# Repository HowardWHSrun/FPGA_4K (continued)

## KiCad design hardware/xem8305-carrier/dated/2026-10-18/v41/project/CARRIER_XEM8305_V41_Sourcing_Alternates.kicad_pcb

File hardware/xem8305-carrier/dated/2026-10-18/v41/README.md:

# XEM8305 carrier V41 — review package

18 October 2026. **Latest saved carrier revision for Gerald's review; fabrication approval is pending.** This is the carrier that connects the XEM8305 to the existing LDO board. It is separate from the standalone FPGA V41, which shares the same version number.

- [Schematic PDF](output/pdf/Carrier_V41_Schematic.pdf)
- [All six copper layers and both silkscreens](output/layers/README.md)
- [Complete public KiCad ZIP](Carrier_V41_Public_KiCad_Review.zip)
- [Native KiCad project](project/CARRIER_XEM8305_V41_Sourcing_Alternates.kicad_pro)
- [Weekend changes, checks and review questions](Review_Context.md)
- [Factory and assembly requirements](Factory_Review_Requirements.md)
- [V41 BOM: 39 groups / 82 fitted references](output/assembly/V41_JLC_BOM_Full_82_Parts_39_MPNs.csv)
- [Placement file](output/assembly/V41_JLC_CPL_Full_82_Parts_Centroids.csv) and [separate shunt accessory](output/assembly/V41_JP1_Shunt_Accessory_Separate.csv)
- [Gerbers, paste and separate PTH/NPTH drills](output/V41_JLC_Gerber_Paste_Drill_Clean.zip)
- [Verification files](verification/)

Extract the complete ZIP before opening the project in KiCad 10.0.6. Keep its project-local libraries and tables together. This public adaptation omits all 3D model references and embedded supplier STEP bodies; the original local V41 is preserved. The schematic, electrical layout, placements, copper, saved fills, stack and rules are checked against the frozen V41 source. The PCB file's complete hash therefore differs from the private source. Missing 3D bodies cannot establish mechanical clearance.

V41 updates ten references in six sourcing groups after capacitor, LED resistor and EEPROM checks. **All V40 routing remains unchanged:** 738 track sections, 312 vias, 651 pads and 21 zones. The earlier silkscreen cleanup, regulator return correction, USB TVS change and JP1 hole/mechanical adaptation are retained.

Saved-board checks report zero physical/silkscreen findings, zero opens and zero schematic/PCB parity findings under the retained settings. Fifty inherited library warnings and 210 inherited unused-connector ERC findings remain documented. Static checks do not establish powered operation, timing, SI/PI, thermal performance or factory acceptance.

Five assembled boards are being quoted. Four exact-part procurement groups, source allocation and the factory stack/via/panel/manual-assembly review remain open. No procurement, order or payment has been made. The included manufacturing files are review candidates, not an approved production release.

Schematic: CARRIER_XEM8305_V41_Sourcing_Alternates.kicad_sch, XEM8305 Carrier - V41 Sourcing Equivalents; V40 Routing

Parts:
C5: 220 uF / 25 V; EEE_FK1E221P; MPN EEE-FK1E221P
C6, C38, C48: 0.1 uF / 50 V; C_0402; MPN CL05B104KB54PNC
C34, C53: 0.1 uF / 10 V; C_0402; MPN C0402C104K8PACTU
C47: 22 uF / 35 V; C_1206; MPN C3216X5R1V226MTJ00E
C49, C50: 22 uF / 10 V; C_1206; MPN LMK316AB7226KL-TR
C54: 10 pF / 50 V; C_0402; MPN CL05C100JB5NNNC
C55: 3.3 nF / 50 V; C_0402; MPN C0402C332K5RACTU
C56: 1 uF / 25 V X7R; C_0603_1608Metric; MPN MSAST168SB7105KTNA01
C500, C501, C505, C511, C513: 4.7uF; C_0402_1005Metric; MPN JMK105BBJ475MV-F
C502, C503, C504, C506, C507, C508, C509, C512, C514, C515, C516, C517, C518, C519, C520, C522, C525, C526, C527, C528: 100nF; C_0402_1005Metric; MPN C0402C104K8PACTU
C510, C521: 10nF; C_0402_1005Metric; MPN CL05B103KB5NNNC
C523, C524: 18pF; C_0402_1005Metric; MPN C0402C180J5GACTU
D4: SMBJ15CA-13-F; D_SMB; MPN SMBJ15CA-13-F
D500: D5V0FS4U10LP-7; Diodes_UDFN-10_1x2.5mm_P0.5mm; MPN D5V0FS4U10LP-7
D501: TPD1E10B06DPYR; TI_DPY0002A_TPD1E10B06; MPN TPD1E10B06DPYR
D600, D601, D602: RED / 0603; LED_0603_Kingbright; MPN APT1608LSECK/J3-PRV
FB500, FB501, FB502: 600R @100MHz; L_0603_1608Metric; MPN MI0603J601R-10
FB503: 220R @100MHz; L_0805_2012Metric; MPN BLM21PG221SN1D
J1: DF40C(2.0)-50DS-0.4V(51); Hirose_DF40C(2.0)-50DS-0.4V_2x25_P0.4mm; MPN DF40C(2.0)-50DS-0.4V(51)
J4: PJ-102AH; PJ102AH; MPN PJ-102AH
J19: DF40C(2.0)-24DS-0.4V(51); Hirose_DF40C(2.0)-24DS-0.4V_2x12_P0.4mm; MPN DF40C(2.0)-24DS-0.4V(51)
J500: USB4110-GF-A; USB_C_Receptacle_GCT_USB4110; MPN USB4110-GF-A
JP1: REMOVE FOR EXT 3V3; Harwin_M20_9990245_1x02_P2_54_HandSolder; MPN M20-9990245
L14: 3.3 uH; Murata_1267AY; MPN 1267AY-3R3N=P3
MC1: ERF6-50-03.5-L-DV-A-K-TR; MPN ERF6-50-03.5-L-DV-A-K-TR
MC2, MC3: ERF6-40-03.5-L-DV-A-K-TR; MPN ERF6-40-03.5-L-DV-A-K-TR
MH1, MH2, MH3, MH4: M3 isolated; MountingHole_3.2mm_M3_Isolated
NT1: COPPER TIE; NetTie_SGND_0p25; MPN N/A - PCB copper net tie
R75: 10.0 k / 1%; R_0402; MPN CRCW040210K0FKED
R77: 73.2 k / 1%; R_0402; MPN CRCW040273K2FKED
R78: 22.1 k / 1%; R_0402; MPN CRCW040222K1FKEDC
R500, R501: 5.1k; R_0402_1005Metric; MPN CRCW04025K10FKEDC
R502: 12k; R_0402_1005Metric; MPN CRCW040212K0FKED
R503, R510: 10k; R_0402_1005Metric; MPN CRCW040210K0FKED
R507, R508: 100k; R_0402_1005Metric; MPN CRCW0402100KFKED
R509: 2k; R_0402_1005Metric; MPN CRCW04022K00FKED
R600: 10k; R_0805; MPN CRCW080510K0FKEA
R601, R602: 1.5k; R_0805; MPN 0805W8F1501T5E
TP19: 3V3 TEST / EXT+; TestPoint_PTH_D1_Pad2_5
TP20: GND / EXT-; TestPoint_PTH_D1_Pad2_5
U10: TPS54429E; TPS54429E_RSA; MPN TPS54429ERSAR
U500, U502, U503, U504: SN74AXC1T45DBVR; SOT-23-6; MPN SN74AXC1T45DBVR
U501: FT232HQ; QFN-48-1EP_8x8mm_P0.5mm_EP6.2x6.2mm; MPN FT232HQ
U505: 93LC56BT-E/MS; MSOP-8_3x3mm_P0.65mm; MPN 93LC56BT-E/MS
Y500: 12MHz / 18pF; Crystal_SMD_3225-4Pin_3.2x2.5mm; MPN ABM8-12.000MHZ-B2-T

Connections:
/CHIP_RESET: J1.14 (CHIP_RESET), MC1.85 (B64_L7N)
/CLK32MHZ: J1.36 (CLK32MHZ), MC1.67 (B64_L11P_GC)
/CLKH: J1.12 (CLKH), MC1.78 (B64_L3N)
/D1: J1.4 (D1), MC1.86 (B64_L1N)
/D2: J1.6 (D2), MC1.84 (B64_L1P)
/D3: J1.8 (D3), MC1.82 (B64_L2N)
/D4: J1.10 (D4), MC1.80 (B64_L2P)
/D5: J1.38 (D5), MC1.70 (B64_L5N)
/D6: J1.40 (D6), MC1.68 (B64_L5P)
/D7: J1.42 (D7), MC1.71 (B64_L10P)
/D8: J1.44 (D8), MC1.69 (B64_L11N_GC)
/FE_RESET: J1.20 (FE_RESET), MC1.83 (B64_L7P)
/IMP_TEST: J1.18 (IMP_TEST), MC1.76 (B64_L3P)
/READ: J1.46 (READ), MC1.65 (B64_L12N_GC)
/SPI_CLK: J1.22 (SPI_CLK), MC1.74 (B64_L4N)
/SPI_DINL: J1.26 (SPI_DINL), MC1.79 (B64_L8P)
/SPI_DINR: J1.28 (SPI_DINR), MC1.72 (B64_L4P)
/SPI_LATCH: J1.24 (SPI_LATCH), MC1.81 (B64_L8N)
/STIM_CHB: J1.33 (STIM_CHB), MC1.64 (B64_L6P)
/STIM_CLK: J1.29 (STIM_CLK), MC1.73 (B64_L10N)
/STIM_EN: J1.31 (STIM_EN), MC1.66 (B64_L6N)
/STIM_START: J1.27 (STIM_START), MC1.75 (B64_L9P)
/SYNC: J1.34 (SYNC), MC1.77 (B64_L9N)
/VBST: C53.1, U10.12 (VBST)
BUCK_3V3: C49.2, C50.2, C54.2, JP1.1 (A), L14.2, R77.2, R602.1, U10.16 (VO)
DGND: C5.2, C6.1, C34.1, C38.1, C47.1, C48.1, C49.1, C50.1, C56.1, C500.1, C501.1, C502.1, C503.1, C504.1, C505.1, C506.1, C507.1, C508.1, C509.1, C510.1, C511.1, C512.1, C513.1, C514.1, C515.1, C516.1, C517.1, C518.1, C519.1, C520.1, C521.1, C522.1, C523.1, C524.1, C525.1, C526.1, C527.1, C528.1, D4.1 (A1), D500.3 (A_3), D500.8 (A_8), D501.2 (IO2), D600.1 (K), D601.1 (K), D602.1 (K), FB503.2, J1.49 (DGND), J1.50 (DGND), J4.2, J500.A1 (GND_A1), J500.A12 (GND_A12), J500.B1 (GND_B1), J500.B12 (GND_B12), MC1.5 (DGND), MC1.6 (DGND), MC1.7 (DGND), MC1.8 (DGND), MC1.33 (DGND), MC1.34 (DGND), MC1.61 (DGND), MC1.62 (DGND), MC1.92 (DGND), MC1.94 (DGND), MC1.96 (DGND), MC1.98 (DGND), MC1.100 (DGND), MC2.6 (DGND), MC2.9 (DGND), MC2.20 (DGND), MC2.35 (DGND), MC2.45 (DGND), MC2.46 (DGND), MC2.47 (DGND), MC2.72 (DGND), MC2.73 (DGND), MC2.74 (DGND), MC2.76 (DGND), MC3.1 (DGND), MC3.2 (DGND), MC3.7 (DGND), MC3.8 (DGND), MC3.13 (DGND), MC3.14 (DGND), MC3.19 (DGND), MC3.20 (DGND), MC3.25 (DGND), MC3.26 (DGND), MC3.31 (DGND), MC3.32 (DGND), MC3.37 (DGND), MC3.38 (DGND), MC3.43 (DGND), MC3.44 (DGND), MC3.49 (DGND), MC3.50 (DGND), MC3.55 (DGND), MC3.56 (DGND), MC3.61 (DGND), MC3.62 (DGND), MC3.67 (DGND), MC3.68 (DGND), MC3.73 (DGND), MC3.74 (DGND), MC3.79 (DGND), MC3.80 (DGND), NT1.2, R500.1, R501.2, R502.1, R508.1, TP20.1, U10.7 (PGND1), U10.8 (PGND2), U10.17 (EP/PGND), U500.2 (GND_2), U501.4 (AGND_4), U501.9 (AGND_9), U501.10 (GND_10), U501.11 (GND_11), U501.22 (GND_22), U501.23 (GND_23), U501.35 (GND_35), U501.36 (GND_36), U501.41 (AGND_41), U501.42 (TEST_42), U501.47 (GND_47), U501.48 (GND_48), U501.49 (EP), U502.2 (GND_2), U503.2 (GND_2), U503.5 (DIR_5), U504.2 (GND_2), U505.5 (VSS_5), Y500.2 (CASE_2), Y500.4 (CASE_4)
GNDADC: MC2.14 (VREFP), MC2.16 (GNDADC)
JTAG_TCK: MC2.1 (JTAG_TCK), U500.4 (B_4)
JTAG_TDI: MC2.3 (JTAG_TDI), U502.4 (B_4)
JTAG_TDO: MC2.7 (JTAG_TDO), U503.4 (B_4)
JTAG_TMS: MC2.5 (JTAG_TMS), U504.4 (B_4)
LDO_3V3: J1.1 (3V3), J1.2 (3V3), JP1.2 (B), R601.1, TP19.1
LED_BUCK3V3_A: D602.2 (A), R602.2
LED_LDO3V3_A: D601.2 (A), R601.2
LED_VDCIN_A: D600.2 (A), R600.2
unnamed: R75.1, U10.6 (EN)
unnamed: C55.2, U10.3 (SS)
unnamed: C53.2, L14.1, U10.9 (SW1), U10.10 (SW2), U10.11 (SW3)
unnamed: C54.1, R77.1, R78.2, U10.1 (VFB)
unnamed: C56.2, U10.2 (VREG5)
SGND_BUCK: C55.1, NT1.1, R78.1, U10.4 (GND)
USBJTAG_3V3: C500.2, C503.2, C507.2, C508.2, C509.2, C513.2, C514.2, C515.2, C519.2, C525.2, C527.2, FB500.1, FB501.1, R503.2, R507.2, R510.2, U500.1 (Vcca_1), U500.5 (DIR_5), U501.12 (VCCIO_12), U501.24 (VCCIO_24), U501.39 (VCCD_39), U501.46 (VCCIO_46), U502.1 (Vcca_1), U502.5 (DIR_5), U503.1 (Vcca_1), U504.1 (Vcca_1), U504.5 (DIR_5), U505.8 (VCC_8)
USBJTAG_CC1: J500.A5 (CC1_A5), R500.2
USBJTAG_CC2: J500.B5 (CC2_B5), R501.1
USBJTAG_EECLK: R507.1, U501.44 (EECLK_44), U505.2 (CLK_2)
USBJTAG_EECS: R508.2, U501.45 (EECS_45), U505.1 (CS_1)
USBJTAG_EEDATA: R509.1, U501.43 (EEDATA_43), U505.3 (DI_3)
USBJTAG_EEPROM_DO: R509.2, R510.1, U505.4 (DO_4)
USBJTAG_ESD_UNUSED: D500.1 (K_1), D500.10 (K_10)
USBJTAG_FT232_RESET: C521.2, R503.1, U501.34 (~RESET_34)
USBJTAG_FTDI_TCK: U500.3 (A_3), U501.13 (ADBUS0_/_TCK_/_SK_13)
USBJTAG_FTDI_TDI: U501.14 (ADBUS1_/_TDI_/_DO_14), U502.3 (A_3)
USBJTAG_FTDI_TDO: U501.15 (ADBUS2_/_TDO_/_DI_15), U503.3 (A_3)
USBJTAG_FTDI_TMS: U501.16 (ADBUS3_/_TMS_/_CS_16), U504.3 (A_3)
USBJTAG_OSCI: C523.2, U501.1 (OSCI_1), Y500.1 (OSC1_1)
USBJTAG_OSCO: C524.2, U501.2 (OSCO_2), Y500.3 (OSC2_3)
USBJTAG_REF: R502.2, U501.5 (REF_5)
USBJTAG_SHIELD: C522.2, FB503.1, J500.SH (SHELL_M4)
USBJTAG_USB_DN: D500.5 (K_5), D500.6 (K_6), J500.A7 (DN1_A7), J500.B7 (DN2_B7), U501.6 (DM_6)
USBJTAG_USB_DP: D500.4 (K_4), D500.7 (K_7), J500.A6 (DP1_A6), J500.B6 (DP2_B6), U501.7 (DP_7)
USBJTAG_VBUS_C: C510.2, D501.1 (IO1), FB502.2, J500.A4 (VBUS_A4), J500.A9 (VBUS_A9), J500.B4 (VBUS_B4), J500.B9 (VBUS_B9)
USBJTAG_VCCA: C518.2, U501.37 (VCCA_37)
USBJTAG_VCORE: C517.2, U501.38 (VCORE_38)
USBJTAG_VPHY: C505.2, C506.2, FB501.2, U501.3 (VPHY_3)
USBJTAG_VPLL: C501.2, C502.2, FB500.2, U501.8 (VPLL_8)
USBJTAG_VREGIN: C511.2, C512.2, FB502.1, U501.40 (VREGIN_40)
VDCIN: C5.1, C6.2, C38.2, C47.2, C48.2, D4.2 (A2), J4.1, MC1.91 (VDCIN), MC1.93 (VDCIN), MC1.95 (VDCIN), MC1.97 (VDCIN), MC1.99 (VDCIN), R75.2, R600.1, U10.13 (VIN1), U10.14 (VIN2), U10.15 (VIN3)
XEM_1V8: C34.2, C504.2, C516.2, C520.2, C526.2, C528.2, MC1.1 (VCCO_84), MC1.2 (VCCO_64), MC1.3 (VCCO_84), MC1.4 (VCCO_64), MC2.37 (VCCO_85), MC2.39 (VCCO_85), MC2.41 (VCCO_86), MC2.43 (VCCO_86), MC2.75 (1V8_OUT), MC2.77 (1V8_OUT), MC2.79 (1V8_OUT), U500.6 (Vccb_6), U502.6 (Vccb_6), U503.6 (Vccb_6), U504.6 (Vccb_6)

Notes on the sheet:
A LDO AND XEM CONNECTORS (J1 / J19 / MC1-MC3)
1. Function: Connect the inherited LDO-board digital interface and 3.3 V feed to the XEM8305; J19 is the retained
auxiliary socket.
B FPGA BANK POWER (C34 / XEM_1V8)
1. Function: Feed FPGA banks 64/84/85/86 from the module-exported 1.8 V at MC2.75/77/79; C34 provides common 100 nF
bypass.
2. Source / changes: Adapted manufacturer BRK8305 A03, main sheet1 (PDFp1), VCCO links and C34:
https://pins.opalkelly.com/downloads/583/download?category_id=3 . Codex integration replaces source R19/R34/R35/R36
(each 0 ohm) with direct wires; C34=0.1 uF/10 V is retained. No added regulator. Module sequencing/current and
ASIC-level compatibility are unverified. Module power guidance:
https://docs.opalkelly.com/xem8305/powering-the-xem8305/ .
C EXTERNAL 3.3 V ACCESS (JP1 / TP19 / TP20)
1. Function: JP1 joins BUCK_3V3 to LDO_3V3; removing its shunt lets a regulated external 3.3 V source feed TP19
relative to TP20.
2. Source / changes: Codex test-access circuit, inherited from V18; JP1 now Harwin M20-9990245 with M7566-05 shunt.
Header DRG-00479, issue 23, sheet 2; shunt DRG-00743, issue 13, sheet 2. Dimensions, ratings and mounting pattern:
https://www.harwin.com/products/M20-9990245 ; https://www.harwin.com/products/M7566-05
Harwin recommends 1.02 +/-0.05 mm finished holes. V40 deliberately uses 1.10 mm holes and retained 1.70 mm lands
for standard JLC +0.13/-0.08 mm hole tolerance and manual soldering. This is a Codex adaptation of the recommended pattern.
D XEM MOUNTS (MH1-MH4)
1. Function: Provide four 3.2 mm plated mounting holes with 6.4 mm isolated copper rings for the XEM stack.
2. Source / changes: Codex mechanical integration, inherited from carrier V18; this is not a datasheet circuit.
Module mounting positions/stack reference: Opal Kelly XEM8305 Specifications, mechanical drawings:
https://docs.opalkelly.com/xem8305/specifications/ . Nominal module connector stack is 5.0 mm; actual standoffs,
mating and assembled clearance remain unverified. No electrical components changed in V20.
E INTERNAL MONITOR REFERENCE
1. Function: Connect module VREFP to module GNDADC to select the internal FPGA monitor reference; keep GNDADC
separate from DGND.
2. Source / changes: Adapted manufacturer BRK8305 A03 main sheet1 (PDFp1), R6 reference link:
https://pins.opalkelly.com/downloads/583/download?category_id=3 . Codex replaces source R6=0 ohm with a direct
wire; no extra reference IC or RC network. Opal Kelly Expansion Connectors, MC2.14/.16:
https://docs.opalkelly.com/xem8305/expansion-connectors/ . Module reference behavior is inherited; powered monitor
operation remains unverified.
F MAIN 12 V INPUT (J4 / C5 / C6 / C38 / D4)
1. Function: Accept center-positive 12 V, distribute VDCIN to XEM MC1.91/93/95/97/99 and the buck input; C5/C6/C38
bypass the rail and D4 shunts transients.
2. Source / changes: Manufacturer BRK8305 A03 main sheet1 (PDFp1), Power Jack and MC1 bypass:
https://pins.opalkelly.com/downloads/583/download?category_id=3 . Inherited source structure/values: C5=220 uF/25 V,
Originally C6=C38=0.1 uF/25 V; D4=SMBJ15CA, J4=PJ-102AH; switched jack pin3 stays open. Codex selects 12 V and omits the
alternative J5 input/indicator circuits. TVS clamping, source ripple/load and assembled input protection remain

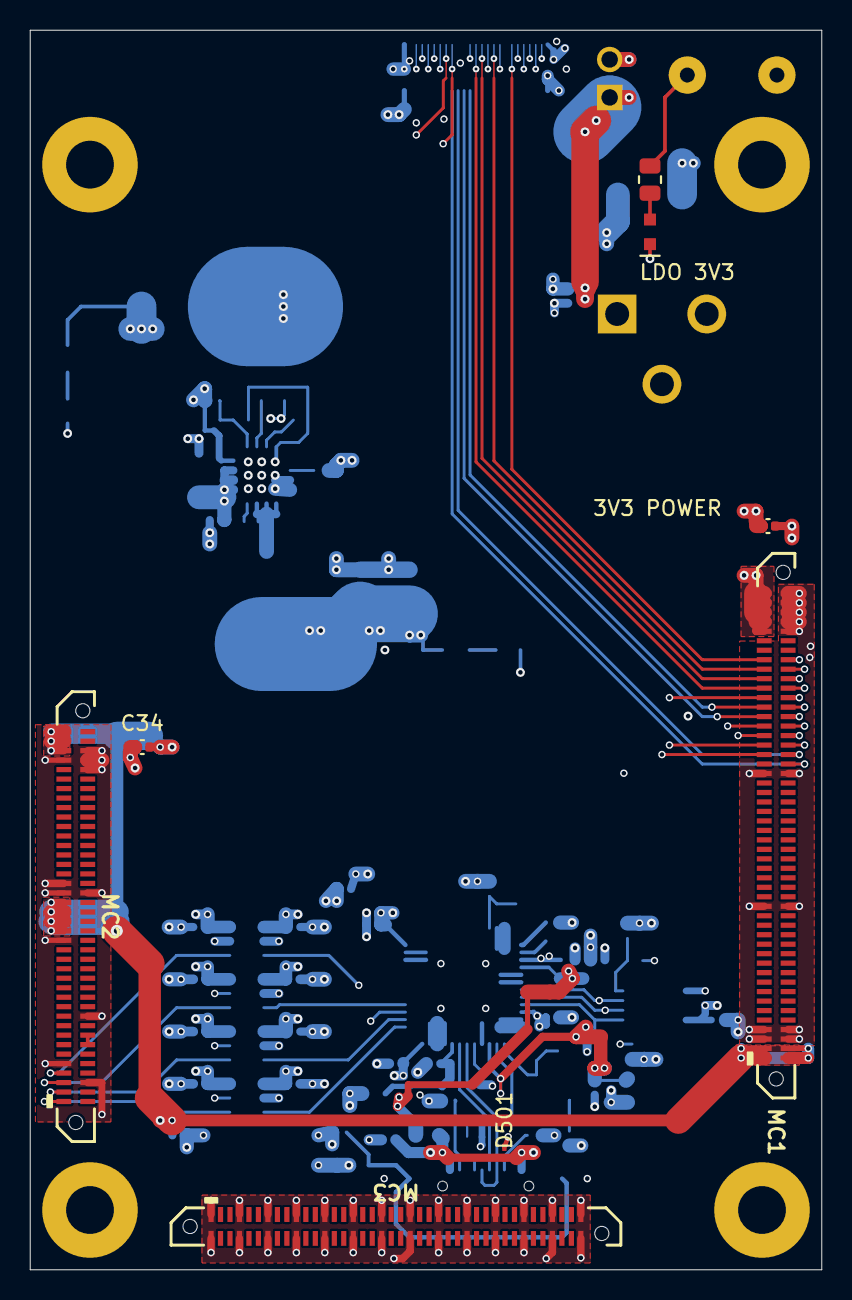
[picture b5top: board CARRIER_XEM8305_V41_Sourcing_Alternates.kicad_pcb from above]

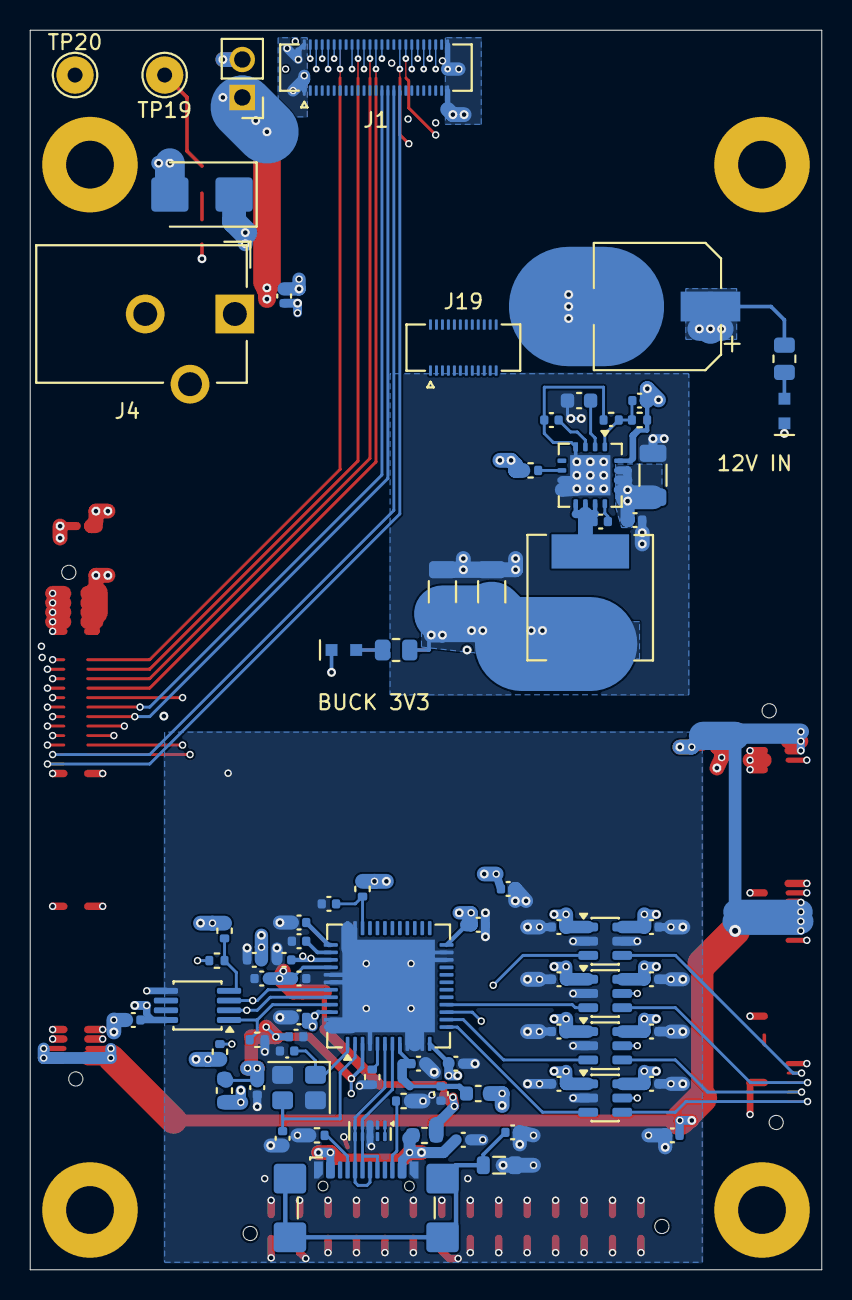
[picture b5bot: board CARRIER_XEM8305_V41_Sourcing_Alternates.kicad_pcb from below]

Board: 6 copper layers, 53.0 x 83.0 mm, 89 parts (77 on the bottom side), 68 nets.

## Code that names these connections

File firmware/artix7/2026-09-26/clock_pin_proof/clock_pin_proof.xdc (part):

# IMPLEMENTATION-ONLY: nominal32MHz test clocks, NOT external ASIC timing signoff.
# No input delay is invented; report_timing_summary will flag unconstrained interface paths.
# No CLOCK_DEDICATED_ROUTE override or DRC downgrade is permitted.
set_property PACKAGE_PIN K1 [get_ports {ASIC1_DATA1}]
set_property IOSTANDARD LVCMOS15 [get_ports {ASIC1_DATA1}]
set_property PACKAGE_PIN F1 [get_ports {ASIC1_DATA2}]
set_property IOSTANDARD LVCMOS15 [get_ports {ASIC1_DATA2}]
set_property PACKAGE_PIN K2 [get_ports {ASIC1_DATA3}]
set_property IOSTANDARD LVCMOS15 [get_ports {ASIC1_DATA3}]
set_property PACKAGE_PIN E1 [get_ports {ASIC1_DATA4}]
set_property IOSTANDARD LVCMOS15 [get_ports {ASIC1_DATA4}]
set_property PACKAGE_PIN H1 [get_ports {ASIC1_DATA5}]
set_property IOSTANDARD LVCMOS15 [get_ports {ASIC1_DATA5}]
set_property PACKAGE_PIN G2 [get_ports {ASIC1_DATA6}]
set_property IOSTANDARD LVCMOS15 [get_ports {ASIC1_DATA6}]
set_property PACKAGE_PIN G1 [get_ports {ASIC1_DATA7}]
set_property IOSTANDARD LVCMOS15 [get_ports {ASIC1_DATA7}]
set_property PACKAGE_PIN C1 [get_ports {ASIC1_DATA8}]
set_property IOSTANDARD LVCMOS15 [get_ports {ASIC1_DATA8}]
set_property PACKAGE_PIN E2 [get_ports {ASIC1_CLK32MHz_Out}]
set_property IOSTANDARD LVCMOS15 [get_ports {ASIC1_CLK32MHz_Out}]
set_property PACKAGE_PIN B1 [get_ports {ASIC1_READ}]
set_property IOSTANDARD LVCMOS15 [get_ports {ASIC1_READ}]
set_property PACKAGE_PIN J2 [get_ports {ASIC1_SYNC}]
set_property IOSTANDARD LVCMOS15 [get_ports {ASIC1_SYNC}]
set_property PACKAGE_PIN C2 [get_ports {ASIC2_DATA1}]
set_property IOSTANDARD LVCMOS15 [get_ports {ASIC2_DATA1}]
set_property PACKAGE_PIN H2 [get_ports {ASIC2_DATA2}]
set_property IOSTANDARD LVCMOS15 [get_ports {ASIC2_DATA2}]
set_property PACKAGE_PIN B3 [get_ports {ASIC2_DATA3}]
set_property IOSTANDARD LVCMOS15 [get_ports {ASIC2_DATA3}]
set_property PACKAGE_PIN J3 [get_ports {ASIC2_DATA4}]
set_property IOSTANDARD LVCMOS15 [get_ports {ASIC2_DATA4}]
set_property PACKAGE_PIN A3 [get_ports {ASIC2_DATA5}]
set_property IOSTANDARD LVCMOS15 [get_ports {ASIC2_DATA5}]
set_property PACKAGE_PIN G3 [get_ports {ASIC2_DATA6}]
set_property IOSTANDARD LVCMOS15 [get_ports {ASIC2_DATA6}]
set_property PACKAGE_PIN C4 [get_ports {ASIC2_DATA7}]
set_property IOSTANDARD LVCMOS15 [get_ports {ASIC2_DATA7}]
set_property PACKAGE_PIN A1 [get_ports {ASIC2_DATA8}]
set_property IOSTANDARD LVCMOS15 [get_ports {ASIC2_DATA8}]
set_property PACKAGE_PIN E3 [get_ports {ASIC2_CLK32MHz_Out}]
set_property IOSTANDARD LVCMOS15 [get_ports {ASIC2_CLK32MHz_Out}]
set_property PACKAGE_PIN B2 [get_ports {ASIC2_READ}]
set_property IOSTANDARD LVCMOS15 [get_ports {ASIC2_READ}]
set_property PACKAGE_PIN B4 [get_ports {ASIC2_SYNC}]
set_property IOSTANDARD LVCMOS15 [get_ports {ASIC2_SYNC}]
set_property PACKAGE_PIN J4 [get_ports {ASIC3_DATA1}]
set_property IOSTANDARD LVCMOS15 [get_ports {ASIC3_DATA1}]
set_property PACKAGE_PIN J5 [get_ports {ASIC3_DATA2}]
set_property IOSTANDARD LVCMOS15 [get_ports {ASIC3_DATA2}]
set_property PACKAGE_PIN H4 [get_ports {ASIC3_DATA3}]
set_property IOSTANDARD LVCMOS15 [get_ports {ASIC3_DATA3}]
set_property PACKAGE_PIN F5 [get_ports {ASIC3_DATA4}]
set_property IOSTANDARD LVCMOS15 [get_ports {ASIC3_DATA4}]
set_property PACKAGE_PIN G4 [get_ports {ASIC3_DATA5}]
set_property IOSTANDARD LVCMOS15 [get_ports {ASIC3_DATA5}]
set_property PACKAGE_PIN E5 [get_ports {ASIC3_DATA6}]
set_property IOSTANDARD LVCMOS15 [get_ports {ASIC3_DATA6}]
set_property PACKAGE_PIN H5 [get_ports {ASIC3_DATA7}]
set_property IOSTANDARD LVCMOS15 [get_ports {ASIC3_DATA7}]
set_property PACKAGE_PIN G6 [get_ports {ASIC3_DATA8}]
set_property IOSTANDARD LVCMOS15 [get_ports {ASIC3_DATA8}]
set_property PACKAGE_PIN F4 [get_ports {ASIC3_CLK32MHz_Out}]
set_property IOSTANDARD LVCMOS15 [get_ports {ASIC3_CLK32MHz_Out}]
set_property PACKAGE_PIN E6 [get_ports {ASIC3_READ}]
set_property IOSTANDARD LVCMOS15 [get_ports {ASIC3_READ}]
set_property PACKAGE_PIN H6 [get_ports {ASIC3_SYNC}]
set_property IOSTANDARD LVCMOS15 [get_ports {ASIC3_SYNC}]
set_property PACKAGE_PIN C5 [get_ports {ASIC4_DATA1}]
set_property IOSTANDARD LVCMOS15 [get_ports {ASIC4_DATA1}]
set_property PACKAGE_PIN A4 [get_ports {ASIC4_DATA2}]
set_property IOSTANDARD LVCMOS15 [get_ports {ASIC4_DATA2}]
set_property PACKAGE_PIN C6 [get_ports {ASIC4_DATA3}]
set_property IOSTANDARD LVCMOS15 [get_ports {ASIC4_DATA3}]
set_property PACKAGE_PIN A5 [get_ports {ASIC4_DATA4}]
set_property IOSTANDARD LVCMOS15 [get_ports {ASIC4_DATA4}]
set_property PACKAGE_PIN A6 [get_ports {ASIC4_DATA5}]
set_property IOSTANDARD LVCMOS15 [get_ports {ASIC4_DATA5}]
set_property PACKAGE_PIN B6 [get_ports {ASIC4_DATA6}]
set_property IOSTANDARD LVCMOS15 [get_ports {ASIC4_DATA6}]
set_property PACKAGE_PIN C7 [get_ports {ASIC4_DATA7}]
set_property IOSTANDARD LVCMOS15 [get_ports {ASIC4_DATA7}]
set_property PACKAGE_PIN E7 [get_ports {ASIC4_DATA8}]
set_property IOSTANDARD LVCMOS15 [get_ports {ASIC4_DATA8}]
set_property PACKAGE_PIN D5 [get_ports {ASIC4_CLK32MHz_Out}]
set_property IOSTANDARD LVCMOS15 [get_ports {ASIC4_CLK32MHz_Out}]
set_property PACKAGE_PIN B7 [get_ports {ASIC4_READ}]
set_property IOSTANDARD LVCMOS15 [get_ports {ASIC4_READ}]
set_property PACKAGE_PIN D8 [get_ports {ASIC4_SYNC}]
set_property IOSTANDARD LVCMOS15 [get_ports {ASIC4_SYNC}]
set_property PACKAGE_PIN V1 [get_ports {ASIC5_DATA1}]
set_property IOSTANDARD LVCMOS15 [get_ports {ASIC5_DATA1}]
set_property PACKAGE_PIN R1 [get_ports {ASIC5_DATA2}]
set_property IOSTANDARD LVCMOS15 [get_ports {ASIC5_DATA2}]
set_property PACKAGE_PIN U1 [get_ports {ASIC5_DATA3}]
set_property IOSTANDARD LVCMOS15 [get_ports {ASIC5_DATA3}]
set_property PACKAGE_PIN U2 [get_ports {ASIC5_DATA4}]
set_property IOSTANDARD LVCMOS15 [get_ports {ASIC5_DATA4}]
set_property PACKAGE_PIN T1 [get_ports {ASIC5_DATA5}]
set_property IOSTANDARD LVCMOS15 [get_ports {ASIC5_DATA5}]
set_property PACKAGE_PIN R2 [get_ports {ASIC5_DATA6}]
set_property IOSTANDARD LVCMOS15 [get_ports {ASIC5_DATA6}]
set_property PACKAGE_PIN V2 [get_ports {ASIC5_DATA7}]
set_property IOSTANDARD LVCMOS15 [get_ports {ASIC5_DATA7}]
set_property PACKAGE_PIN U3 [get_ports {ASIC5_DATA8}]
set_property IOSTANDARD LVCMOS15 [get_ports {ASIC5_DATA8}]
set_property PACKAGE_PIN R3 [get_ports {ASIC5_CLK32MHz_Out}]
set_property IOSTANDARD LVCMOS15 [get_ports {ASIC5_CLK32MHz_Out}]
set_property PACKAGE_PIN V4 [get_ports {ASIC5_READ}]
set_property IOSTANDARD LVCMOS15 [get_ports {ASIC5_READ}]
set_property PACKAGE_PIN P2 [get_ports {ASIC5_SYNC}]
set_property IOSTANDARD LVCMOS15 [get_ports {ASIC5_SYNC}]
set_property PACKAGE_PIN M2 [get_ports {ASIC6_DATA1}]
set_property IOSTANDARD LVCMOS15 [get_ports {ASIC6_DATA1}]
set_property PACKAGE_PIN N1 [get_ports {ASIC6_DATA2}]
set_property IOSTANDARD LVCMOS15 [get_ports {ASIC6_DATA2}]
set_property PACKAGE_PIN M3 [get_ports {ASIC6_DATA3}]
set_property IOSTANDARD LVCMOS15 [get_ports {ASIC6_DATA3}]
set_property PACKAGE_PIN M1 [get_ports {ASIC6_DATA4}]
set_property IOSTANDARD LVCMOS15 [get_ports {ASIC6_DATA4}]
set_property PACKAGE_PIN K3 [get_ports {ASIC6_DATA5}]
set_property IOSTANDARD LVCMOS15 [get_ports {ASIC6_DATA5}]
set_property PACKAGE_PIN L1 [get_ports {ASIC6_DATA6}]
set_property IOSTANDARD LVCMOS15 [get_ports {ASIC6_DATA6}]
set_property PACKAGE_PIN N4 [get_ports {ASIC6_DATA7}]
set_property IOSTANDARD LVCMOS15 [get_ports {ASIC6_DATA7}]
set_property PACKAGE_PIN N2 [get_ports {ASIC6_DATA8}]
set_property IOSTANDARD LVCMOS15 [get_ports {ASIC6_DATA8}]
set_property PACKAGE_PIN P4 [get_ports {ASIC6_CLK32MHz_Out}]
set_property IOSTANDARD LVCMOS15 [get_ports {ASIC6_CLK32MHz_Out}]
set_property PACKAGE_PIN L3 [get_ports {ASIC6_READ}]
set_property IOSTANDARD LVCMOS15 [get_ports {ASIC6_READ}]
set_property PACKAGE_PIN R6 [get_ports {ASIC6_SYNC}]
set_property IOSTANDARD LVCMOS15 [get_ports {ASIC6_SYNC}]
set_property PACKAGE_PIN U4 [get_ports {ASIC7_DATA1}]
set_property IOSTANDARD LVCMOS15 [get_ports {ASIC7_DATA1}]
set_property PACKAGE_PIN V7 [get_ports {ASIC7_DATA2}]
set_property IOSTANDARD LVCMOS15 [get_ports {ASIC7_DATA2}]
set_property PACKAGE_PIN V5 [get_ports {ASIC7_DATA3}]
set_property IOSTANDARD LVCMOS15 [get_ports {ASIC7_DATA3}]
set_property PACKAGE_PIN U7 [get_ports {ASIC7_DATA4}]
set_property IOSTANDARD LVCMOS15 [get_ports {ASIC7_DATA4}]
set_property PACKAGE_PIN V6 [get_ports {ASIC7_DATA5}]
set_property IOSTANDARD LVCMOS15 [get_ports {ASIC7_DATA5}]
set_property PACKAGE_PIN U8 [get_ports {ASIC7_DATA6}]
set_property IOSTANDARD LVCMOS15 [get_ports {ASIC7_DATA6}]
set_property PACKAGE_PIN U6 [get_ports {ASIC7_DATA7}]
set_property IOSTANDARD LVCMOS15 [get_ports {ASIC7_DATA7}]
set_property PACKAGE_PIN V9 [get_ports {ASIC7_DATA8}]
set_property IOSTANDARD LVCMOS15 [get_ports {ASIC7_DATA8}]
set_property PACKAGE_PIN T5 [get_ports {ASIC7_CLK32MHz_Out}]
set_property IOSTANDARD LVCMOS15 [get_ports {ASIC7_CLK32MHz_Out}]
set_property PACKAGE_PIN U9 [get_ports {ASIC7_READ}]
set_property IOSTANDARD LVCMOS15 [get_ports {ASIC7_READ}]
set_property PACKAGE_PIN T6 [get_ports {ASIC7_SYNC}]
set_property IOSTANDARD LVCMOS15 [get_ports {ASIC7_SYNC}]
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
